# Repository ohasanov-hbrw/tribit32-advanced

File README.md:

# tribit32-advanced

A tri-microcontroller, overengineered GameBoy Advance clone. More value was given to the controls and the exterior look, which is cool!

## Introduction

This guide is more about the software side of the project. The 3D-Designs and the KiCad files can be found in their respective folders and be edited as needed. This project is as open source as I can make it to be, so if something is missing, message me and I will try to add it here. It would still like builds using this guide to mention me and link to this guide, so thanks in advance!

## Electronics

This section includes information about the electronics I used for the project. This project can be built in three ways: just a single board computer, just the microcontroller, or both at once. Doing both increases difficulty exponentially, so it is not really recommended and is more of a showpiece. 

### Microcontrollers and Single Board Computers

The custom PCB is laid out for an ESP32-S3-DevkitC and Raspberry Pi Zero 2W. If you can make alternatives work with adapters / custom software, you can use that too. However this project focuses more on these two specific boards. 

If you are going to be including a Raspberry Pi, you will also need to get an Arduino Pro Mini for the controller emulation. 

### Periphery

- **ILI9341 3.2inch *non-touch* SPI LCD**: 320x240 16 Bit Color, rated for 10 MHz SPI but most comfortably can run at ~67 MHz. ST7789 might work, but definitely not tested.
- **MAX98357A I2S DAC**: A pretty ok DAC + Amplifier combo. PCM5102 might work too, but these modules are cheap anyway.
- **Micro SD Adapter**: Only needed for ESP32. 
- **2x 4 ohm 20x30 mm Speakers**: Connected in series they enable rich sound.

### Power

- **5 V / 3.3 V Regulators**: Please do not use LDOs or linear regulators. These are inneficient. If just running the Raspberry Pi you can technically forego the 3.3 V Regulator and just use a 5 V one, as the Pi already has (a weak) one on board. Or even better? Use an MH-CD42 Li-Ion charger module with the onboard regulator. Less parts mean less things to solder!
- **Li-Ion Charger**: I originally used a TP4056 which did technically work fine, but after finishing the project I found out better alternatives exist that dont really have that much difference in price. Just get an MH-CD42!
### Other Components

- **6 mm Silicone Buttons**: You can also use different alternatives, the PCB should be able to support them with minimal modifications to the buttons.
- **100 ohm, 10 kohm and 100 kohm Resistors**: Values are actually not that important, something in the ballpark should work. Used mainly for pullups, resistor divider for battery monitoring...
- **Wires**: Use what you have...
- **2.54 mm male and female headers**: You can also totally do the project without any female or even any headers, but you can make pretty much everything dissasemble-able using these. 
- **BC547 NPN Transistors**: Really only needed if you are building a two-board system. 

### PCB

This project is mainly thought out to be built with a custom PCB. Although it is technically possible to make this with normal perfboards as all used components are through hole components (no SMD components), a PCB makes the assembly process a lot faster whilst also resulting in a cleaner build. 

The PCBs for my build were manufactured by [NextPCB](https://www.nextpcb.com/). Thanks a lot for them sending over the PCBs and thus motivating me to design my own PCBs for my future projects. 

## Software Guide

This section will be divided into two subsections. Software for the ESP32 and Software for the Raspberry Pi

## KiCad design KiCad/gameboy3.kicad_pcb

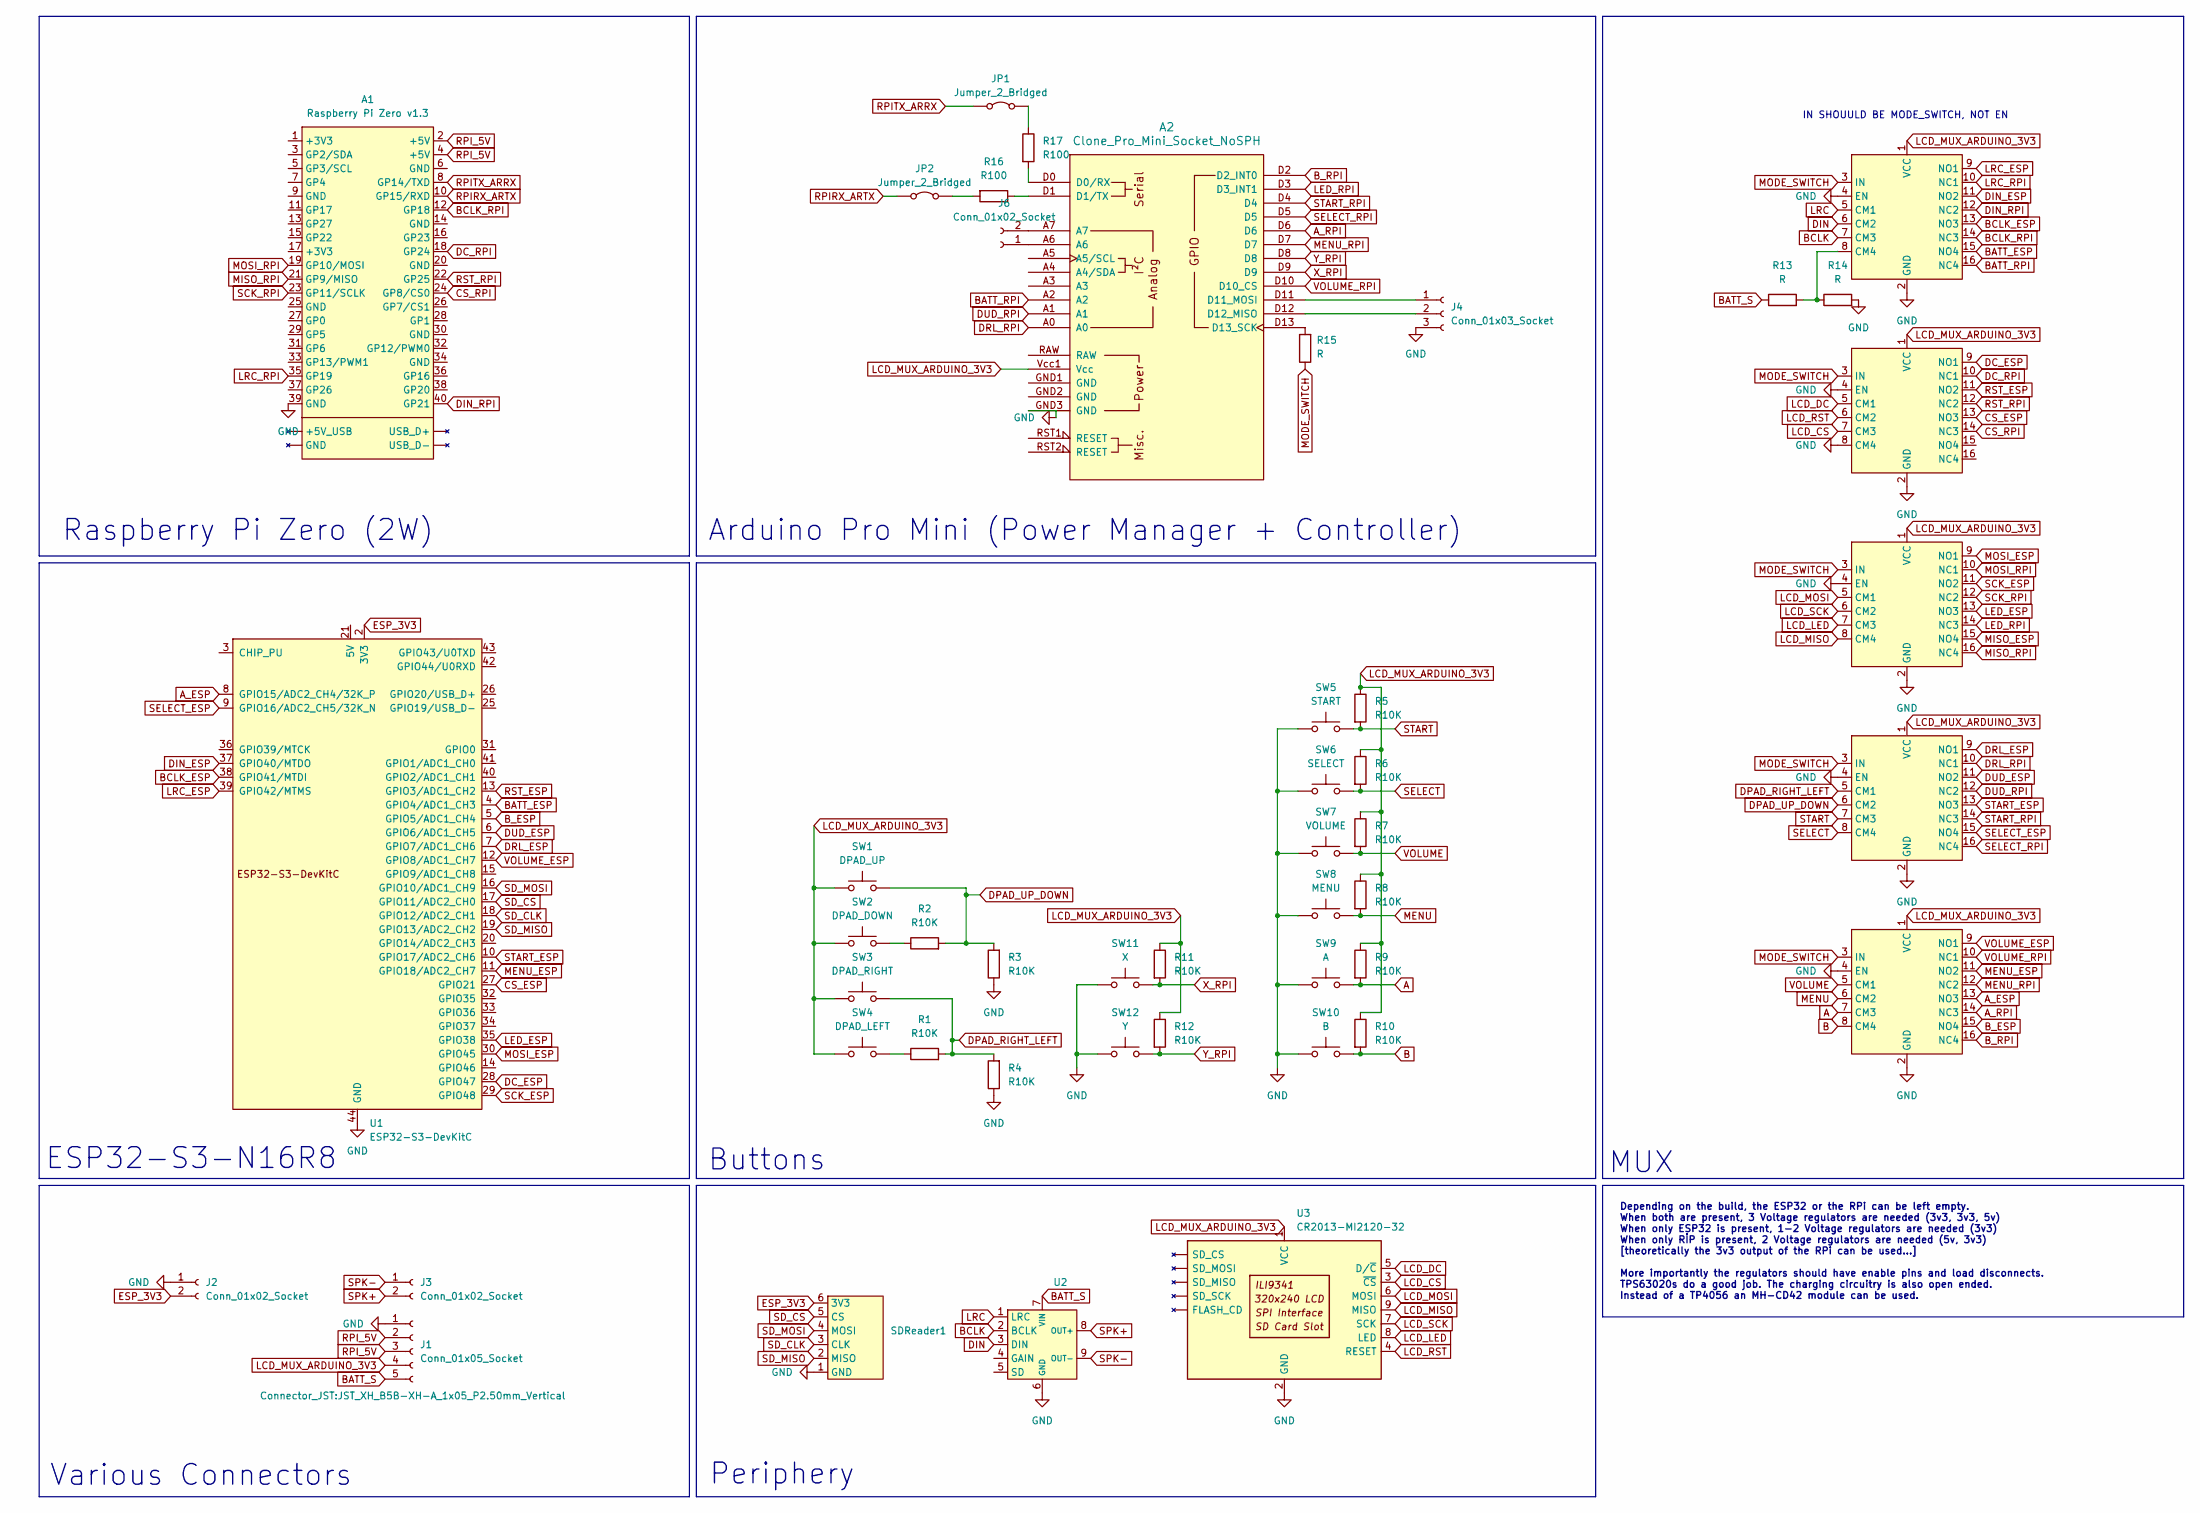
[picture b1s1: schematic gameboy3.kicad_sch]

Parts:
A1: Raspberry Pi Zero v1.3; Raspberry_Pi_Zero
A2: Clone_Pro_Mini_Socket_NoSPH
J1: Conn_01x05_Socket; JST_XH_B5B-XH-A_1x05_P2.50mm_Vertical
J2, J3, J6: Conn_01x02_Socket; JST_XH_B2B-XH-A_1x02_P2.50mm_Vertical
J4: Conn_01x03_Socket; JST_XH_B3B-XH-A_1x03_P2.50mm_Vertical
JP1, JP2: Jumper_2_Bridged; SolderJumper-2_P1.3mm_Open_RoundedPad1.0x1.5mm
R1, R2, R3, R4, R5, R6, R7, R8, R9, R10, R11, R12: R10K; R_Axial_DIN0207_L6.3mm_D2.5mm_P10.16mm_Horizontal
R13, R14, R15: R; R_Axial_DIN0207_L6.3mm_D2.5mm_P10.16mm_Horizontal
R16, R17: R100; R_Axial_DIN0207_L6.3mm_D2.5mm_P10.16mm_Horizontal
SDReader1: SDReader
SW1: DPAD_UP; PUSH_BUTTON
SW2: DPAD_DOWN; PUSH_BUTTON
SW3: DPAD_RIGHT; PUSH_BUTTON
SW4: DPAD_LEFT; PUSH_BUTTON
SW5: START; PUSH_BUTTON
SW6: SELECT; PUSH_BUTTON
SW7: VOLUME; PUSH_BUTTON
SW8: MENU; PUSH_BUTTON
SW9: A; PUSH_BUTTON
SW10: B; PUSH_BUTTON
SW11: X; PUSH_BUTTON
SW12: Y; PUSH_BUTTON
TS3A1, TS3A2, TS3A3, TS3A4, TS3A5: TS3A5018_Module
U1: ESP32-S3-DevKitC
U2: MAX_I2S
U3: CR2013-MI2120-32

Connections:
A: R9.2, SW9.2, TS3A4.7 (CM3)
A_ESP: TS3A4.13 (NO3), U1.8 (GPIO15/ADC2_CH4/32K_P)
A_RPI: A2.D6, TS3A4.14 (NC3)
B: R10.2, SW10.2, TS3A4.8 (CM4)
BATT_ESP: TS3A5.15 (NO4), U1.4 (GPIO4/ADC1_CH3)
BATT_RPI: A2.A2, TS3A5.16 (NC4)
BATT_S: J1.5, R13.1, U2.7 (VIN)
BCLK: TS3A5.7 (CM3), U2.2 (BCLK)
BCLK_ESP: TS3A5.13 (NO3), U1.38 (GPIO41/MTDI)
BCLK_RPI: A1.12 (GP18), TS3A5.14 (NC3)
B_ESP: TS3A4.15 (NO4), U1.5 (GPIO5/ADC1_CH4)
B_RPI: A2.D2 (D2_INT0), TS3A4.16 (NC4)
CS_ESP: TS3A2.13 (NO3), U1.27 (GPIO21)
CS_RPI: A1.24 (GP8/CS0), TS3A2.14 (NC3)
DC_ESP: TS3A2.9 (NO1), U1.28 (GPIO47)
DC_RPI: A1.18 (GP24), TS3A2.10 (NC1)
DIN: TS3A5.6 (CM2), U2.3 (DIN)
DIN_ESP: TS3A5.11 (NO2), U1.37 (GPIO40/MTDO)
DIN_RPI: A1.40 (GP21), TS3A5.12 (NC2)
DPAD_RIGHT_LEFT: R1.2, R4.2, SW3.2, TS3A3.5 (CM1)
DPAD_UP_DOWN: R2.2, R3.2, SW1.2, TS3A3.6 (CM2)
DRL_ESP: TS3A3.9 (NO1), U1.7 (GPIO7/ADC1_CH6)
DRL_RPI: A2.A0, TS3A3.10 (NC1)
DUD_ESP: TS3A3.11 (NO2), U1.6 (GPIO6/ADC1_CH5)
DUD_RPI: A2.A1, TS3A3.12 (NC2)
ESP_3V3: J2.2, SDReader1.6 (3V3), U1.1 (3V3), U1.2 (3V3)
GND: A1.39 (GND), A2.GND3 (GND), J1.1, J2.1, J4.3, R3.1, R4.1, R14.2, SDReader1.1 (GND), SW5.1, SW6.1, SW7.1, SW8.1, SW9.1, SW10.1, SW11.1, SW12.1, TS3A1.2 (GND), TS3A1.4 (EN), TS3A2.2 (GND), TS3A2.4 (EN), TS3A2.8 (CM4), TS3A3.2 (GND), TS3A3.4 (EN), TS3A4.2 (GND), TS3A4.4 (EN), TS3A5.2 (GND), TS3A5.4 (EN), U1.22 (GND), U1.23 (GND), U1.24 (GND), U1.44 (GND), U2.6 (GND), U3.2 (GND)
LCD_CS: TS3A2.7 (CM3), U3.3 (~CS)
LCD_DC: TS3A2.5 (CM1), U3.5 (D/~C)
LCD_LED: TS3A1.7 (CM3), U3.8 (LED)
LCD_MISO: TS3A1.8 (CM4), U3.9 (MISO)
LCD_MOSI: TS3A1.5 (CM1), U3.6 (MOSI)
LCD_MUX_ARDUINO_3V3: A2.Vcc1 (Vcc), J1.4, R5.1, R6.1, R7.1, R8.1, R9.1, R10.1, R11.1, R12.1, SW1.1, SW2.1, SW3.1, SW4.1, TS3A1.1 (VCC), TS3A2.1 (VCC), TS3A3.1 (VCC), TS3A4.1 (VCC), TS3A5.1 (VCC), U3.1 (VCC)
LCD_RST: TS3A2.6 (CM2), U3.4 (RESET)
LCD_SCK: TS3A1.6 (CM2), U3.7 (SCK)
LED_ESP: TS3A1.13 (NO3), U1.35 (GPIO38)
LED_RPI: A2.D3 (D3_INT1), TS3A1.14 (NC3)
LRC: TS3A5.5 (CM1), U2.1 (LRC)
LRC_ESP: TS3A5.9 (NO1), U1.39 (GPIO42/MTMS)
LRC_RPI: A1.35 (GP19), TS3A5.10 (NC1)
MENU: R8.2, SW8.2, TS3A4.6 (CM2)
MENU_ESP: TS3A4.11 (NO2), U1.11 (GPIO18/ADC2_CH7)
MENU_RPI: A2.D7, TS3A4.12 (NC2)
MISO_ESP: TS3A1.15 (NO4)
MISO_RPI: A1.21 (GP9/MISO), TS3A1.16 (NC4)
MODE_SWITCH: R15.1, TS3A1.3 (IN), TS3A2.3 (IN), TS3A3.3 (IN), TS3A4.3 (IN), TS3A5.3 (IN)
MOSI_ESP: TS3A1.9 (NO1), U1.30 (GPIO45)
MOSI_RPI: A1.19 (GP10/MOSI), TS3A1.10 (NC1)
unnamed: A2.D0 (D0/RX), R17.2
unnamed: A2.D1 (D1/TX), R16.1
unnamed: A2.D11 (D11_MOSI), J4.1
unnamed: A2.D12 (D12_MISO), J4.2
unnamed: A2.D13 (D13_SCK), R15.2
unnamed: A2.A6, J6.1
unnamed: A2.A7, J6.2
unnamed: JP1.2 (B), R17.1
unnamed: JP2.2 (B), R16.2
unnamed: R1.1, SW4.2
unnamed: R2.1, SW2.2
unnamed: R13.2, R14.1, TS3A5.8 (CM4)
RPIRX_ARTX: A1.10 (GP15/RXD), JP2.1 (A)
RPITX_ARRX: A1.8 (GP14/TXD), JP1.1 (A)
RPI_5V: A1.2 (+5V), A1.4 (+5V), J1.2, J1.3
RST_ESP: TS3A2.11 (NO2), U1.13 (GPIO3/ADC1_CH2)
RST_RPI: A1.22 (GP25), TS3A2.12 (NC2)
SCK_ESP: TS3A1.11 (NO2), U1.29 (GPIO48)
SCK_RPI: A1.23 (GP11/SCLK), TS3A1.12 (NC2)
SD_CLK: SDReader1.3 (CLK), U1.18 (GPIO12/ADC2_CH1)
SD_CS: SDReader1.5 (CS), U1.17 (GPIO11/ADC2_CH0)
SD_MISO: SDReader1.2 (MISO), U1.19 (GPIO13/ADC2_CH2)
SD_MOSI: SDReader1.4 (MOSI), U1.16 (GPIO10/ADC1_CH9)
SELECT: R6.2, SW6.2, TS3A3.8 (CM4)
SELECT_ESP: TS3A3.15 (NO4), U1.9 (GPIO16/ADC2_CH5/32K_N)
SELECT_RPI: A2.D5, TS3A3.16 (NC4)
SPK+: J3.2, U2.8 (OUT+)
SPK-: J3.1, U2.9 (OUT-)
START: R5.2, SW5.2, TS3A3.7 (CM3)
START_ESP: TS3A3.13 (NO3), U1.10 (GPIO17/ADC2_CH6)
START_RPI: A2.D4, TS3A3.14 (NC3)
VOLUME: R7.2, SW7.2, TS3A4.5 (CM1)
VOLUME_ESP: TS3A4.9 (NO1), U1.12 (GPIO8/ADC1_CH7)
VOLUME_RPI: A2.D10 (D10_CS), TS3A4.10 (NC1)
X_RPI: A2.D9, R11.2, SW11.2
Y_RPI: A2.D8, R12.2, SW12.2

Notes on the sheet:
Depending on the build, the ESP32 or the RPi can be left empty. When both are present, 3 Voltage regulators are needed (3v3, 3v3, 5v) When only ESP32 is present, 1-2 Voltage regulators are needed (3v3) When only RİP is present, 2 Voltage regulators are needed (5v, 3v3) [theoretically the 3v3 output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
Various Connectors
Periphery
Buttons
IN SHOUULD BE MODE_SWITCH, NOT EN
ESP32-S3-N16R8
Raspberry Pi Zero (2W)
Arduino Pro Mini (Power Manager + Controller)
MUX

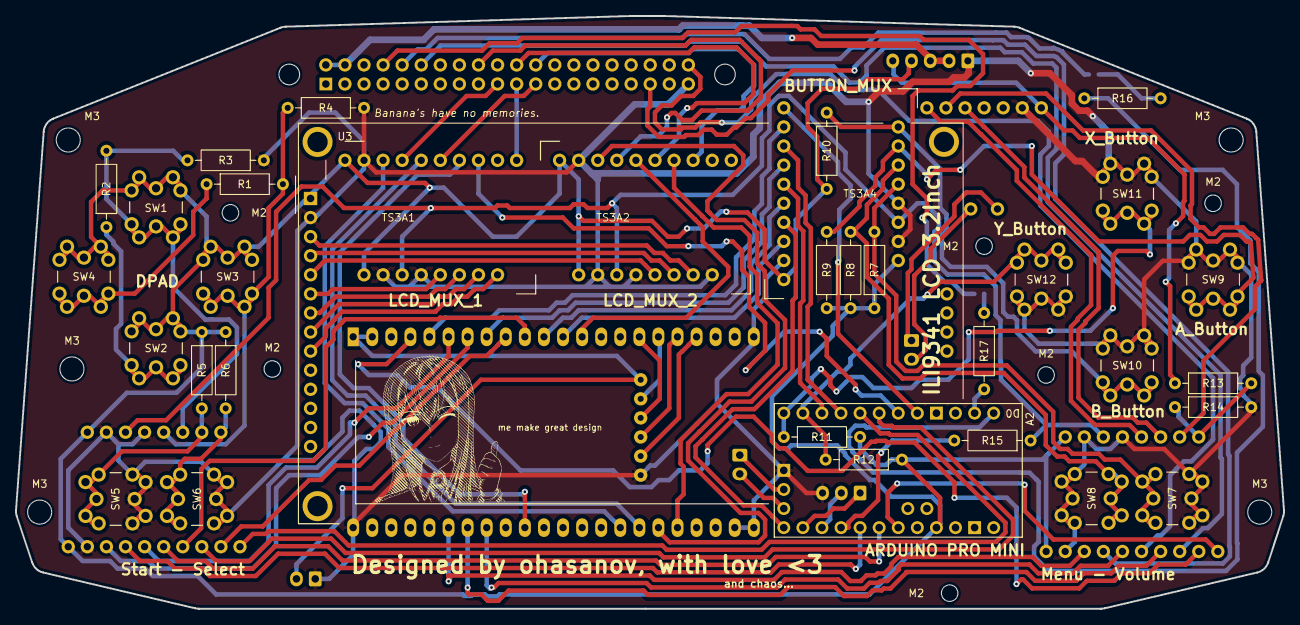
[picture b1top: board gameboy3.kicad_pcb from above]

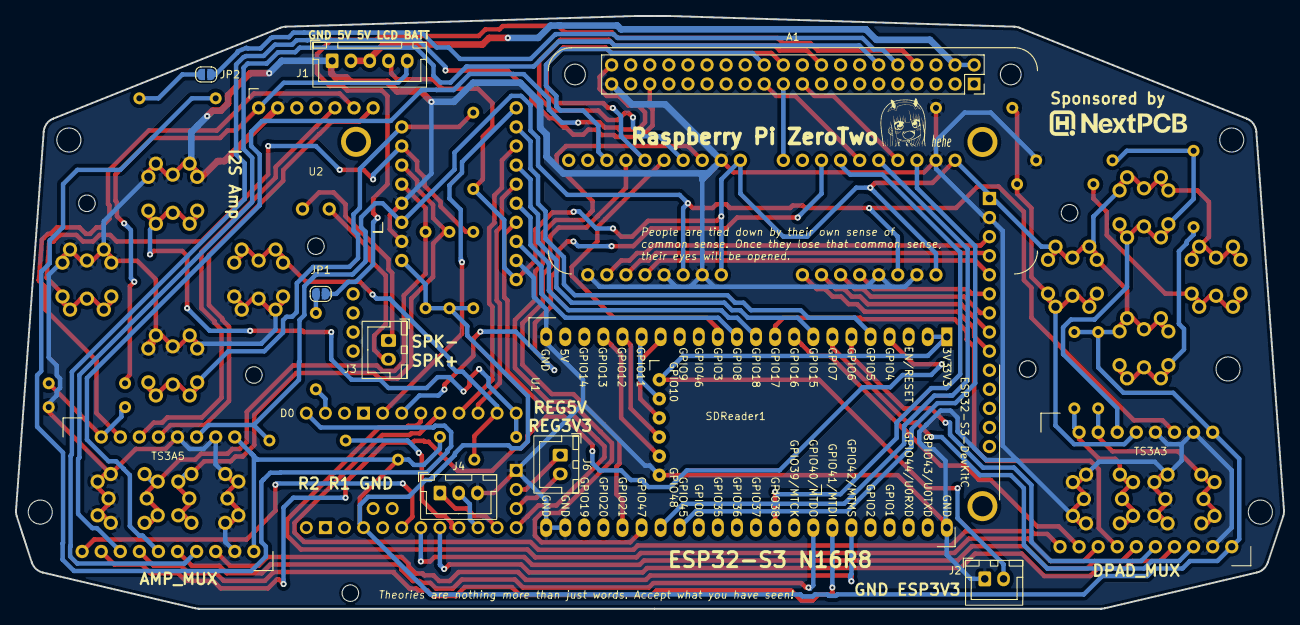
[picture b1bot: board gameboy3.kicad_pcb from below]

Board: 2 copper layers, 168.8 x 78.9 mm, 61 parts (15 on the bottom side), 83 nets.

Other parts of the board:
M2, M2#2, M2#3, M2#4, M2#5, M2#6: MountingHole_2.2mm_M2_DIN965
M3, M3#2, M3#3, M3#4, M3#5: MountingHole_3.2mm_M3_DIN965
Sponsored by: LOGO
hehe: LOGO
me make great design: LOGO
